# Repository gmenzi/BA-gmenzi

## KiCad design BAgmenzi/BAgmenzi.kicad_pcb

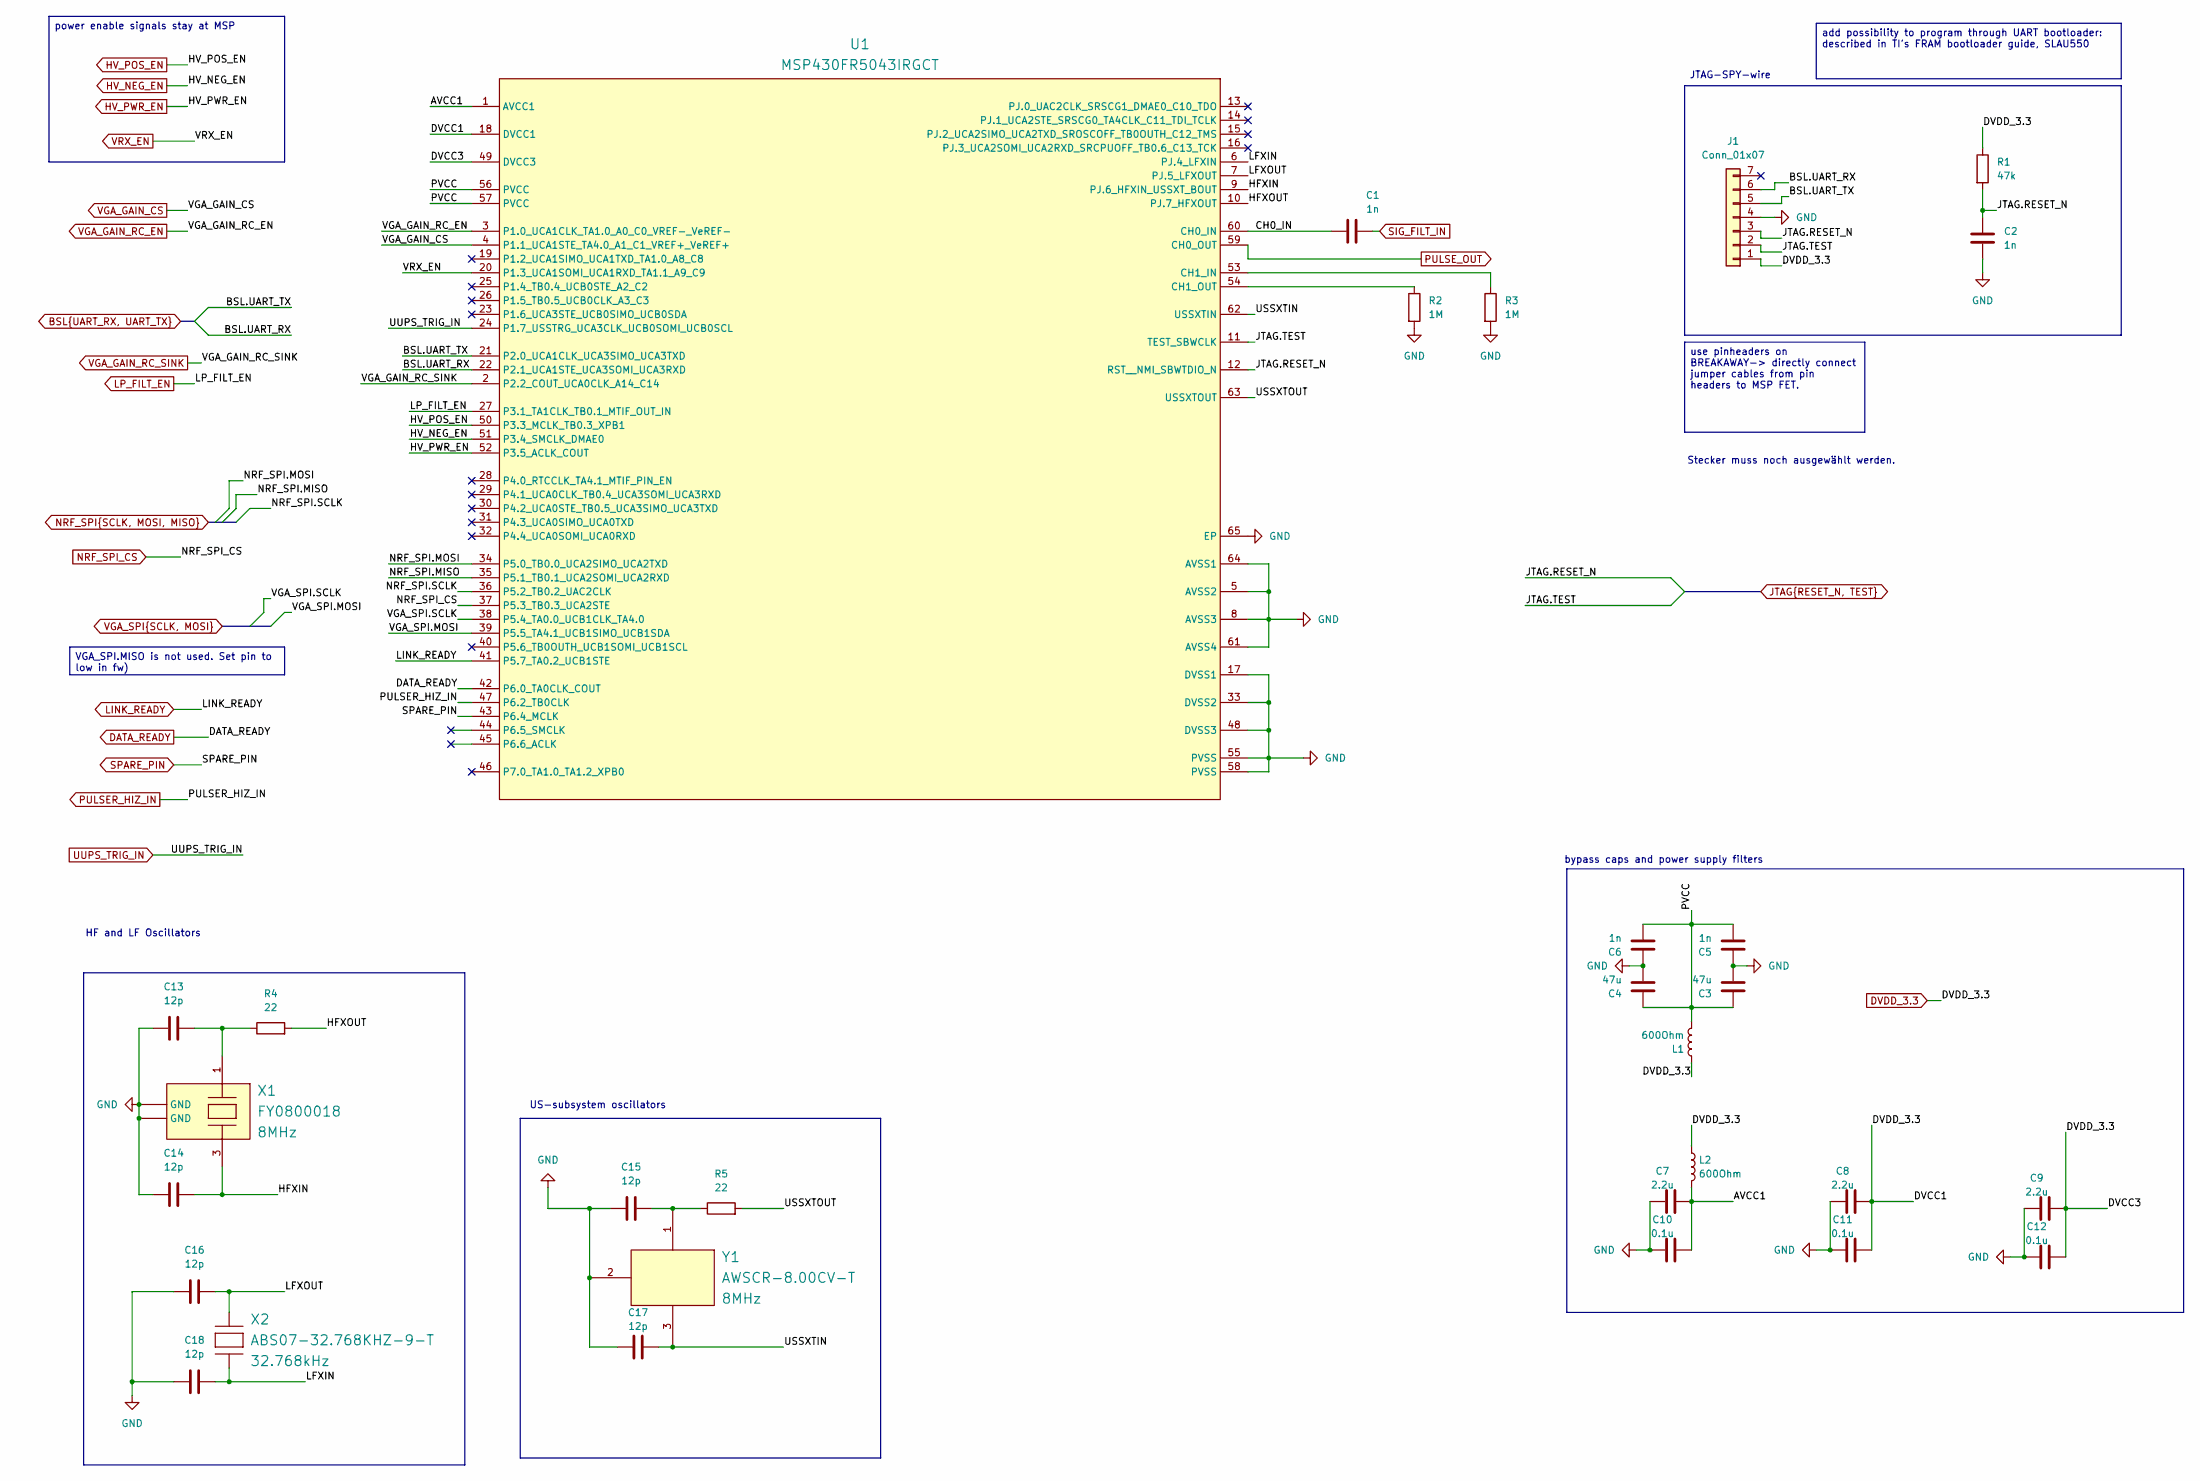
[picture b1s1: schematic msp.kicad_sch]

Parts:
C1, C2, C5, C6: 1n; C_0402_1005Metric; LCSC Part # C76947
C3, C4: 47u; C_0603_1608Metric; LCSC Part # C730416
C7, C8, C9: 2.2u; C_0402_1005Metric; LCSC Part # C77002
C10, C11, C12: 0.1u; C_0402_1005Metric; LCSC Part # C1525
C13, C14, C15, C16, C17, C18: 12p; C_0402_1005Metric; LCSC Part # C161305
J1: Conn_01x07; PinHeader_1x07_P2.54mm_Vertical_SMD_Pin1Right; LCSC Part # C2883764
L1, L2: 600Ohm; SMD-0805; LCSC Part # C41556732
R1: 47k; R_0402_1005Metric; LCSC Part # C482184
R2, R3: 1M; R_0402_1005Metric; LCSC Part # C413126
R4, R5: 22; R_0402_1005Metric; LCSC Part # C114765
U1: MSP430FR5043IRGCT; RGC0064G; Manufacturer_Part_Number MSP430FR5043IRGCT; LCSC Part # C5218420
X1: FY0800018; XTAL_ECS-80-18-30B-AGN-TR; Frequency Tolerance 30ppm; Manufacturer Part Number FY0800018; LCSC Part # C6951614
X2: ABS07-32.768KHZ-9-T; XTAL320X150X90; Frequency Tolerance 20ppm; Tolerance 20ppm; Manufacturer Part Number ABS07-32.768KHZ-9-T; LCSC Part # C179635
Y1: AWSCR-8.00CV-T; AWSCR-8.00CV-T_ABR; Manufacturer_Part_Number AWSCR-8.00CV-T; LCSC Part # C2650764

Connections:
/MSP/AVCC1: C7.2, C10.2, L2.2, U1.1 (AVCC1)
/MSP/CH0_IN: C1.1, U1.60 (CH0_IN)
/MSP/HFXIN: C14.2, U1.9 (PJ.6_HFXIN_USSXT_BOUT), X1.3 (OUT/IN)
/MSP/HFXOUT: R4.2, U1.10 (PJ.7_HFXOUT)
/MSP/LFXIN: C18.2, U1.6 (PJ.4_LFXIN), X2.1
/MSP/LFXOUT: C16.2, U1.7 (PJ.5_LFXOUT), X2.2
/MSP/PVCC: C3.1, C4.1, C5.2, C6.2, L1.2, U1.56 (PVCC), U1.57 (PVCC)
/MSP/USSXTIN: C17.2, U1.62 (USSXTIN), Y1.3
/MSP/USSXTOUT: R5.2, U1.63 (USSXTOUT)
BSL.UART_RX: J1.6, U1.22 (P2.1_UCA1STE_UCA3SOMI_UCA3RXD); also elsewhere on the board
BSL.UART_TX: J1.5, U1.21 (P2.0_UCA1CLK_UCA3SIMO_UCA3TXD); also elsewhere on the board
DATA_READY: U1.42 (P6.0_TA0CLK_COUT); also elsewhere on the board
DVDD_3.3: C8.2, C9.2, C11.2, C12.2, J1.1, L1.1, L2.1, R1.1, U1.18 (DVCC1), U1.49 (DVCC3); also elsewhere on the board
GND: C2.2, C3.2, C4.2, C5.1, C6.1, C7.1, C8.1, C9.1, C10.1, C11.1, C12.1, C13.1, C14.1, C15.1, C16.1, C17.1, C18.1, J1.4, R2.2, R3.2, U1.5 (AVSS2), U1.8 (AVSS3), U1.17 (DVSS1), U1.33 (DVSS2), U1.48 (DVSS3), U1.55 (PVSS), U1.58 (PVSS), U1.61 (AVSS4), U1.64 (AVSS1), U1.65 (EP), X1.2 (GND), X1.4 (GND), Y1.2; also elsewhere on the board
HV_NEG_EN: U1.51 (P3.4_SMCLK_DMAE0); also elsewhere on the board
HV_POS_EN: U1.50 (P3.3_MCLK_TB0.3_XPB1); also elsewhere on the board
HV_PWR_EN: U1.52 (P3.5_ACLK_COUT); also elsewhere on the board
JTAG.RESET_N: C2.1, J1.3, R1.2, U1.12 (RST__NMI_SBWTDIO_N); also elsewhere on the board
JTAG.TEST: J1.2, U1.11 (TEST_SBWCLK); also elsewhere on the board
LINK_READY: U1.41 (P5.7_TA0.2_UCB1STE); also elsewhere on the board
LP_FILT_EN: U1.27 (P3.1_TA1CLK_TB0.1_MTIF_OUT_IN); also elsewhere on the board
NRF_SPI.MISO: U1.35 (P5.1_TB0.1_UCA2SOMI_UCA2RXD); also elsewhere on the board
NRF_SPI.MOSI: U1.34 (P5.0_TB0.0_UCA2SIMO_UCA2TXD); also elsewhere on the board
NRF_SPI.SCLK: U1.36 (P5.2_TB0.2_UAC2CLK); also elsewhere on the board
NRF_SPI_CS: U1.37 (P5.3_TB0.3_UCA2STE); also elsewhere on the board
unnamed: C15.2, R5.1, Y1.1
unnamed: R3.1, U1.53 (CH1_IN)
unnamed: R2.1, U1.54 (CH1_OUT)
unnamed: C13.2, R4.1, X1.1 (IN/OUT)
PULSER_HIZ_IN: U1.47 (P6.2_TB0CLK); also elsewhere on the board
PULSE_OUT: U1.59 (CH0_OUT); also elsewhere on the board
SIG_FILT_IN: C1.2; also elsewhere on the board
SPARE_PIN: U1.43 (P6.4_MCLK); also elsewhere on the board
UUPS_TRIG_IN: U1.24 (P1.7_USSTRG_UCA3CLK_UCB0SOMI_UCB0SCL); also elsewhere on the board
VGA_GAIN_CS: U1.4 (P1.1_UCA1STE_TA4.0_A1_C1_VREF+_VeREF+); also elsewhere on the board
VGA_GAIN_RC_EN: U1.3 (P1.0_UCA1CLK_TA1.0_A0_C0_VREF-_VeREF-); also elsewhere on the board
VGA_GAIN_RC_SINK: U1.2 (P2.2_COUT_UCA0CLK_A14_C14); also elsewhere on the board
VGA_SPI.MOSI: U1.39 (P5.5_TA4.1_UCB1SIMO_UCB1SDA); also elsewhere on the board
VGA_SPI.SCLK: U1.38 (P5.4_TA0.0_UCB1CLK_TA4.0); also elsewhere on the board
VRX_EN: U1.20 (P1.3_UCA1SOMI_UCA1RXD_TA1.1_A9_C9); also elsewhere on the board

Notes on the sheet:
bypass caps and power supply filters
US-subsystem oscillators
JTAG-SPY-wire
Stecker muss noch ausgewählt werden.
HF and LF Oscillators
use pinheaders on BREAKAWAY-> directly connect jumper cables from pin headers to MSP FET.
VGA_SPI.MISO is not used. Set pin to low in fw)
add possibility to program through UART bootloader: described in TI's FRAM bootloader guide, SLAU550
power enable signals stay at MSP

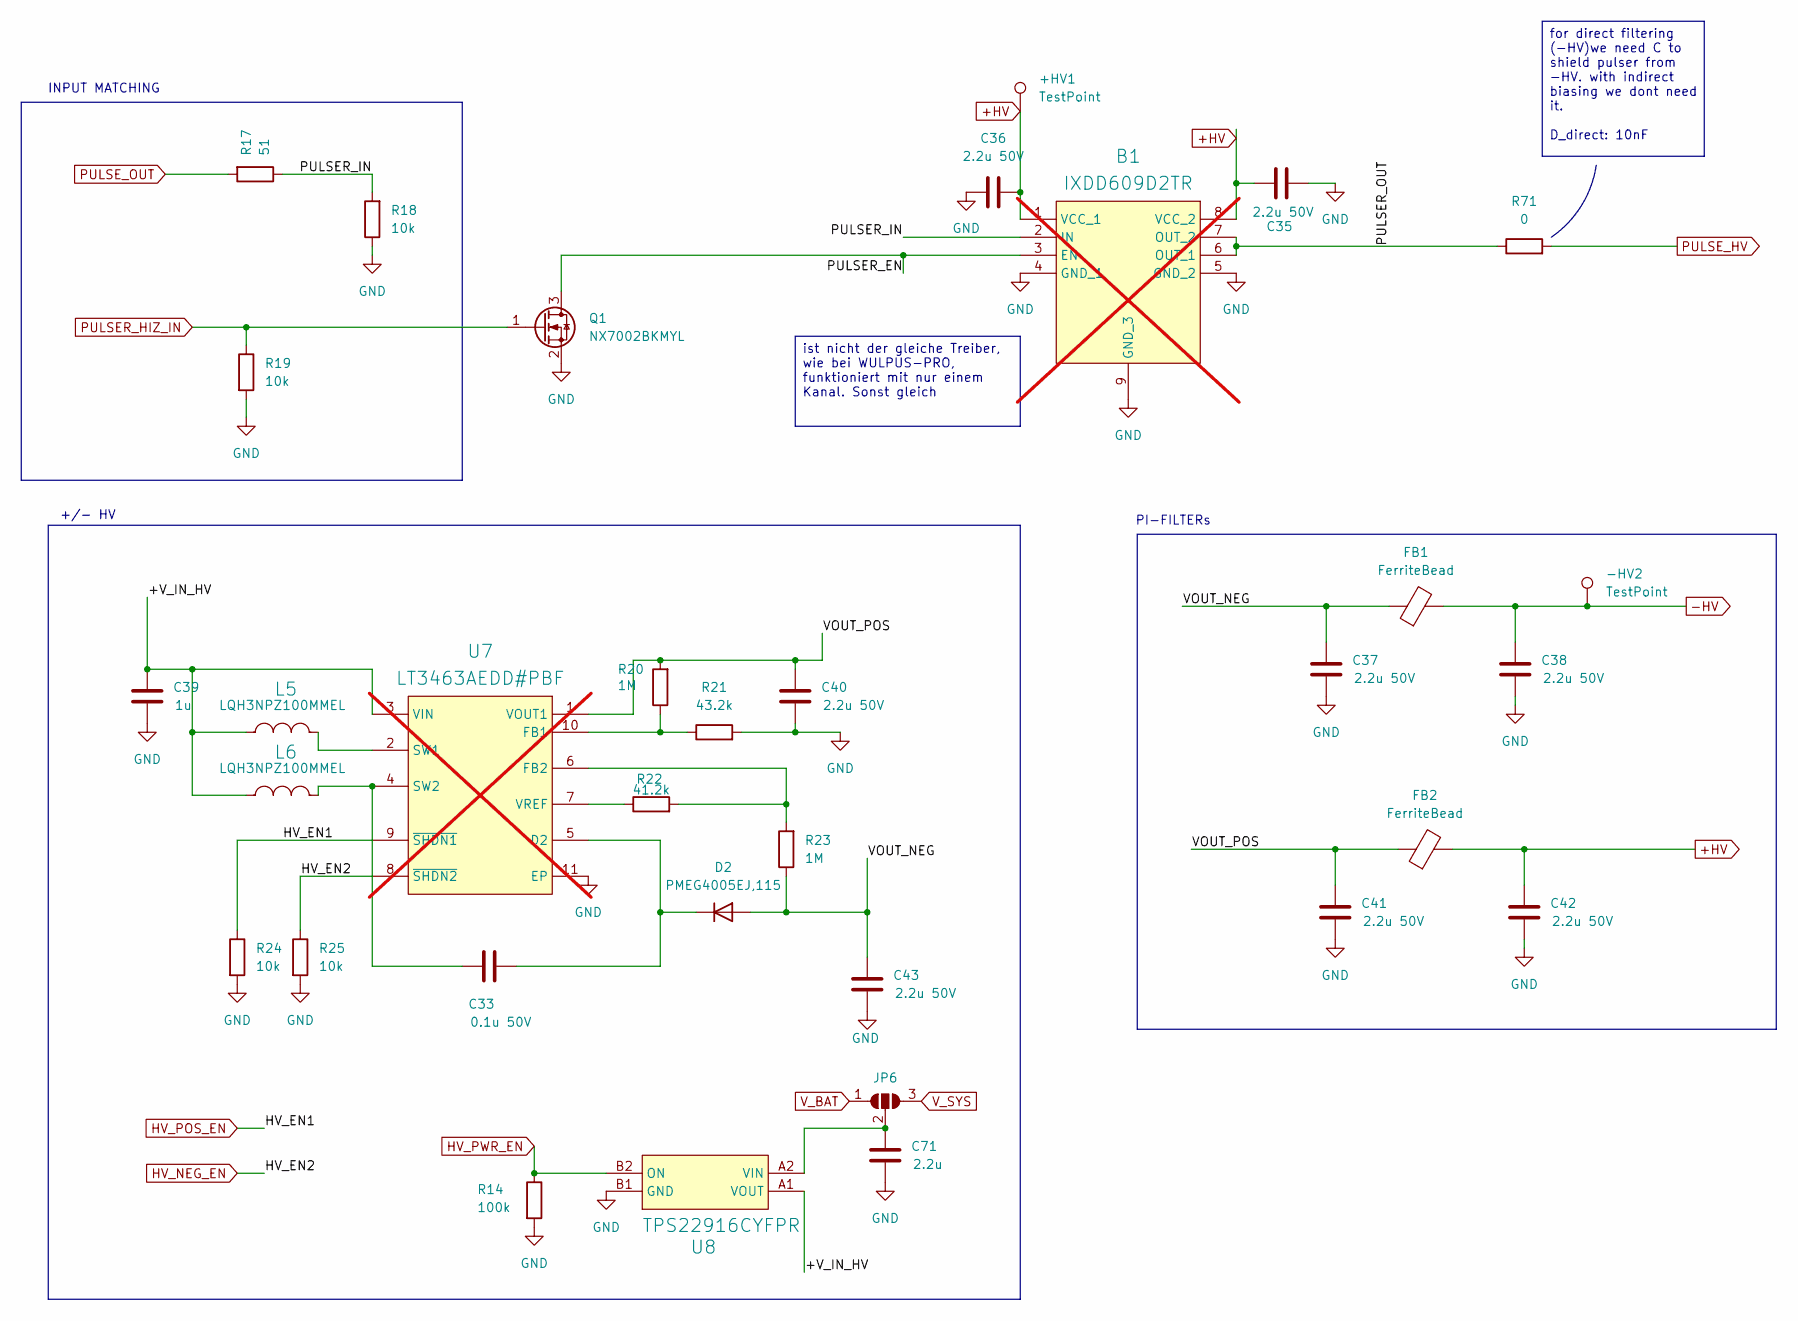
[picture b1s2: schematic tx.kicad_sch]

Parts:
+HV1: TestPoint; TestPoint_Pad_D1.0mm
-HV2: TestPoint; TestPoint_Pad_D1.0mm
B1: IXDD609D2TR; SON95P500X400X100-9N; Manufacturer_Part_Number IXDD609D2TR; LCSC Part # C2653792; not fitted
C33: 0.1u 50V; C_0402_1005Metric; LCSC Part # C913614
C35, C36, C37, C38, C40, C41, C42, C43: 2.2u 50V; C_0603_1608Metric; LCSC Part # C668357
C39: 1u; C_0402_1005Metric; LCSC Part # C14445
C71: 2.2u; C_0402_1005Metric; LCSC Part # C77002
D2: PMEG4005EJ,115; D_SOD-323_HandSoldering; LCSC Part # C426868
FB1, FB2: FerriteBead; L_0603_1608Metric; LCSC Part # C3717002
JP6: SolderJumper_3_Open; SolderJumper-3_P1.3mm_Open_Pad1.0x1.5mm
L5, L6: LQH3NPZ100MMEL; FP-LQH3NPH_ME-MFG; Current Rating 170mA; Manufacturer Part Number LQP15MN3N9B02D; LCSC Part # C701168
Q1: NX7002BKMYL; NX7002BKMBYL; LCSC Part # C551611
R14: 100k; R_0402_1005Metric; LCSC Part # C192169
R17: 51; R_0402_1005Metric; LCSC Part # C482204
R18, R19, R24, R25: 10k; R_0402_1005Metric; LCSC Part # C191984
R20, R23: 1M; R_0402_1005Metric; LCSC Part # C413126
R21: 43.2k; R_0402_1005Metric; LCSC Part # C278596
R22: 41.2k; R_0402_1005Metric; LCSC Part # C416536
R71: 0; R_0402_1005Metric; LCSC Part # C190119
U7: LT3463AEDD#PBF; LT-DD-10_V; PartNumber LT3463AEDD#PBF; LCSC Part # C580060; not fitted
U8: TPS22916CYFPR; BGA4C40P2X2_78X78X50; Manufacturer_Part_Number TPS22916CYFPR; LCSC Part # C2680319

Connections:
+HV: +HV1.1, B1.1 (VCC_1), B1.8 (VCC_2), C35.2, C36.2, C42.1, FB2.2; also elsewhere on the board
-HV: -HV2.1, C38.1, FB1.2; also elsewhere on the board
/TX/+V_IN_HV: C39.1, L5.1, L6.1, U7.3 (VIN), U8.A1 (VOUT)
/TX/PULSER_EN: B1.3 (EN), Q1.3 (D)
/TX/PULSER_IN: B1.2 (IN), R17.1, R18.2
/TX/PULSER_OUT: B1.6 (OUT_1), B1.7 (OUT_2), R71.1
/TX/VOUT_NEG: C37.1, C43.1, D2.2 (A), FB1.1, R23.1
/TX/VOUT_POS: C40.1, C41.1, FB2.1, R20.2, U7.1 (VOUT1)
GND: B1.4 (GND_1), B1.5 (GND_2), B1.9 (GND_3), C35.1, C36.1, C37.2, C38.2, C39.2, C40.2, C41.2, C42.2, C43.2, C71.2, Q1.2 (S), R14.2, R18.1, R19.2, R21.2, R24.2, R25.2, U7.11 (EP), U8.B1 (GND); also elsewhere on the board
HV_NEG_EN: R25.1, U7.8 (~SHDN2); also elsewhere on the board
HV_POS_EN: R24.1, U7.9 (~SHDN1); also elsewhere on the board
HV_PWR_EN: R14.1, U8.B2 (ON); also elsewhere on the board
unnamed: C33.1, D2.1 (K), U7.5 (D2)
unnamed: C71.1, JP6.2 (C), U8.A2 (VIN)
unnamed: R20.1, R21.1, U7.10 (FB1)
unnamed: R22.2, R23.2, U7.6 (FB2)
unnamed: L5.2, U7.2 (SW1)
unnamed: C33.2, L6.2, U7.4 (SW2)
unnamed: R22.1, U7.7 (VREF)
PULSER_HIZ_IN: Q1.1 (G), R19.1; also elsewhere on the board
PULSE_HV: R71.2; also elsewhere on the board
PULSE_OUT: R17.2; also elsewhere on the board
V_BAT: JP6.1 (A); also elsewhere on the board
V_SYS: JP6.3 (B); also elsewhere on the board

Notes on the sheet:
INPUT MATCHING
+/- HV
PI-FILTERs
ist nicht der gleiche Treiber, wie bei WULPUS-PRO, funktioniert mit nur einem Kanal. Sonst gleich
for direct filtering (-HV)we need C to shield pulser from -HV. with indirect biasing we dont need it. D_direct: 10nF

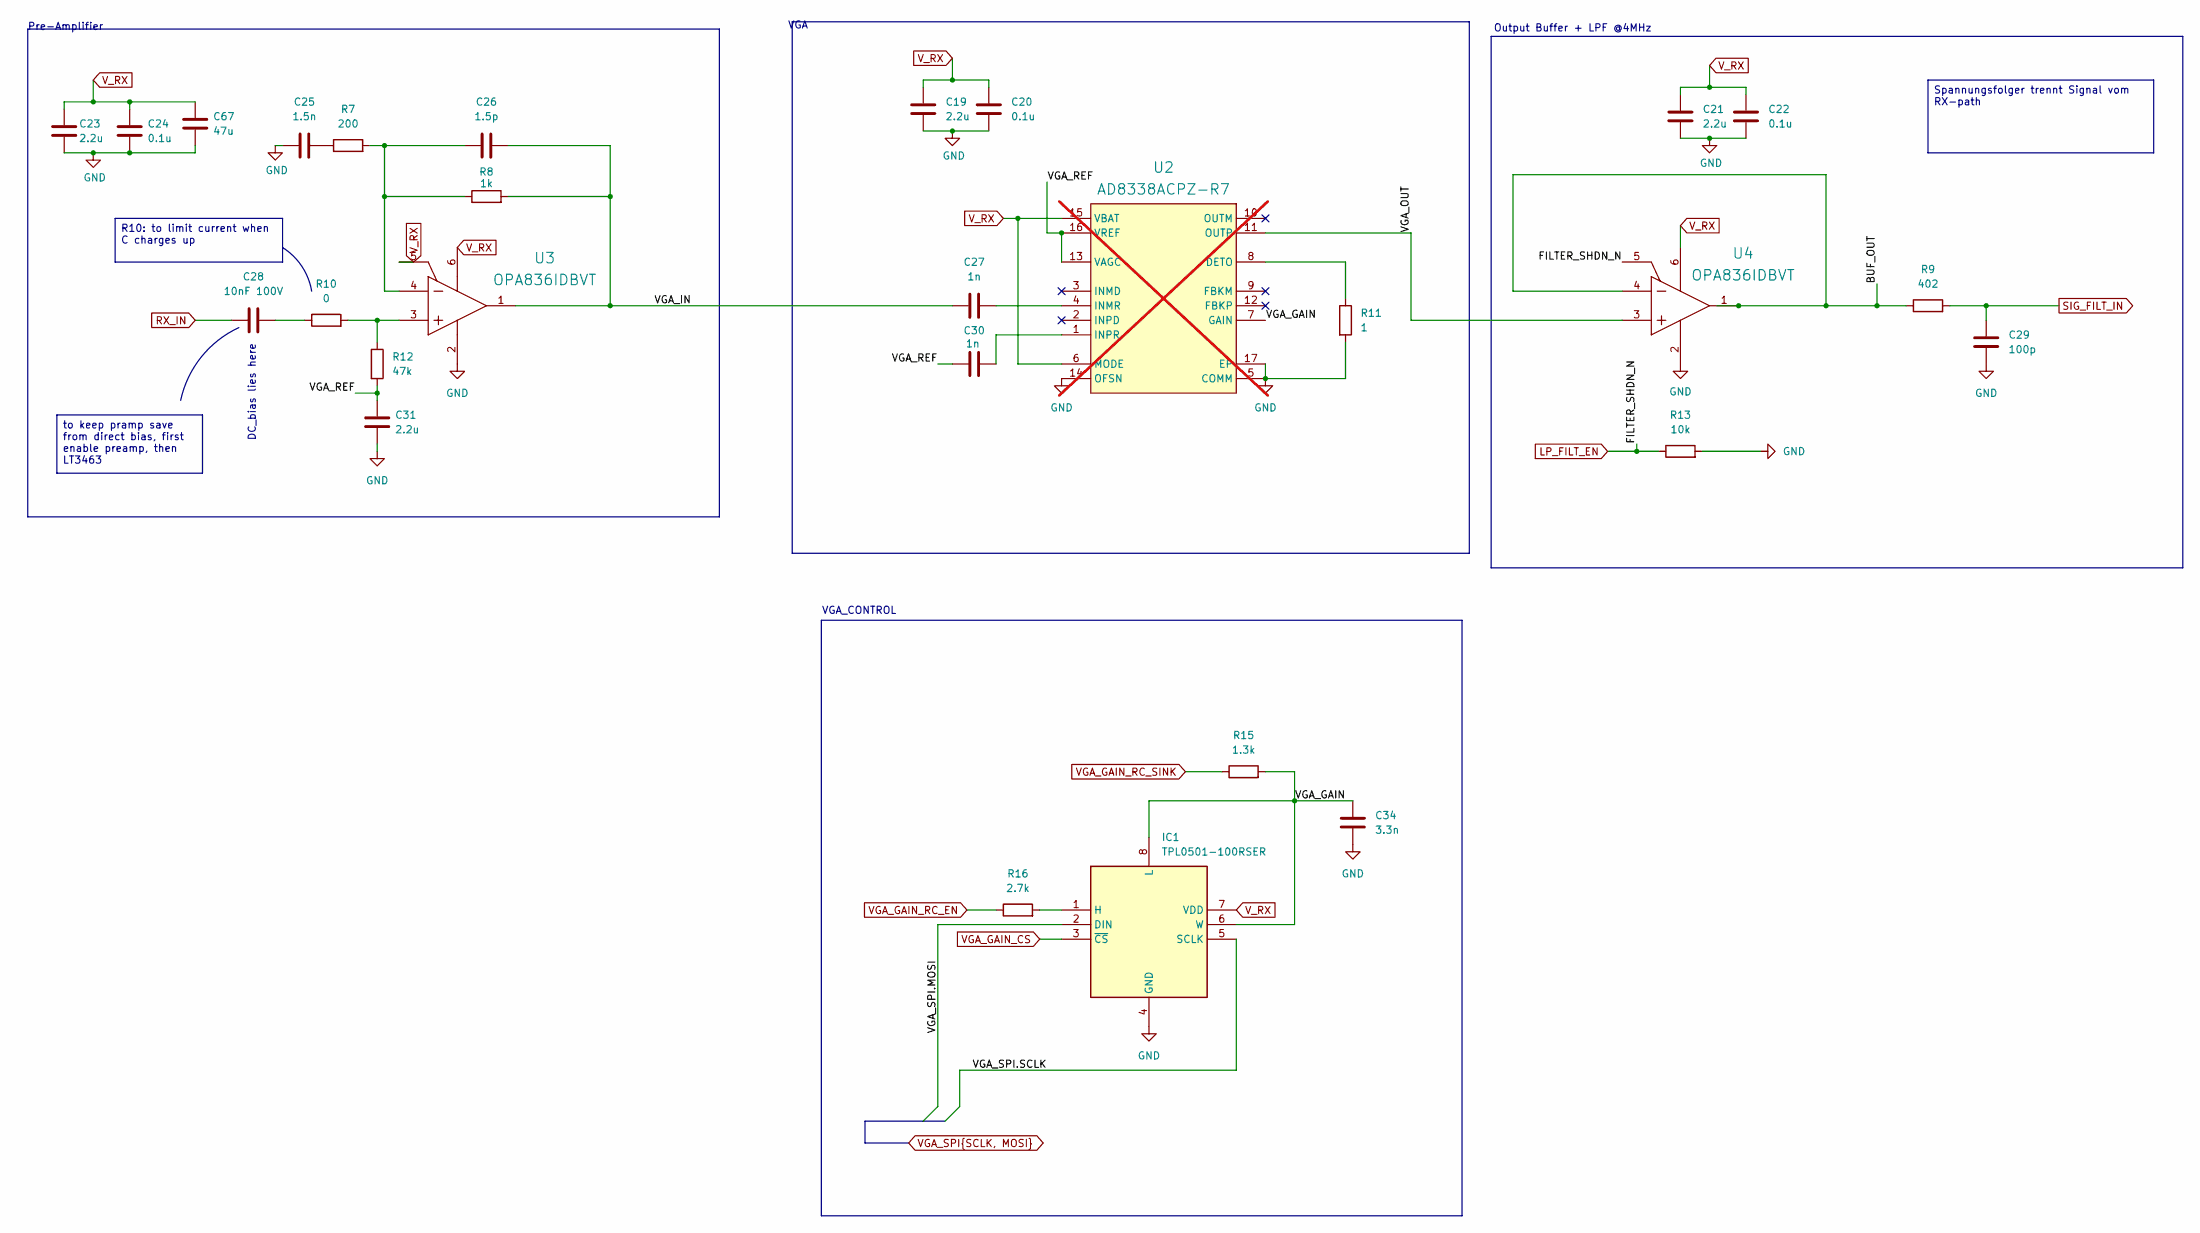
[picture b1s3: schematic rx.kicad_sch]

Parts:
C19, C21, C23, C31: 2.2u; C_0402_1005Metric; LCSC Part # C77002
C20, C22, C24: 0.1u; C_0402_1005Metric; LCSC Part # C1525
C25: 1.5n; C_0402_1005Metric; LCSC Part # C23967
C26: 1.5p; C_0402_1005Metric; LCSC Part # C76900
C27, C30: 1n; C_0402_1005Metric; LCSC Part # C76947
C28: 10nF 100V; C_0402_1005Metric; LCSC Part # C2167243
C29: 100p; C_0402_1005Metric; LCSC Part # C1546
C34: 3.3n; C_0402_1005Metric; LCSC Part # C26404
C67: 47u; C_0603_1608Metric; LCSC Part # C730416
IC1: TPL0501-100RSER; RSE0008A; Manufacturer_Part_Number TPL0501-100RSER; Mouser Part Number 595-TPL0501-100RSER
R7: 200; R_0402_1005Metric; LCSC Part # C25087
R8: 1k; R_0402_1005Metric; LCSC Part # C11702
R9: 402; R_0402_1005Metric; LCSC Part # C41042
R10: 0; R_0402_1005Metric; LCSC Part # C190119
R11: 1; R_0402_1005Metric; LCSC Part # C2077765
R12: 47k; R_0402_1005Metric; LCSC Part # C482184
R13: 10k; R_0402_1005Metric; LCSC Part # C191984
R15: 1.3k; R_0402_1005Metric; LCSC Part # C25866
R16: 2.7k; R_0402_1005Metric; LCSC Part # C2074348
U2: AD8338ACPZ-R7; FP-CP-16-22-IPC_C; Voltage Gain 80dB; Manufacturer Part Number AD8338ACPZ-R7; Mouser Description Special Purpose Amplifiers Ultra Low Pw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; not fitted
U3, U4: OPA836IDBVT; DBV0006A_L; PartNumber OPA836IDBVT; LCSC Part # C2057515

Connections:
/RX/BUF_OUT: R9.1, U4.1 (VOUT), U4.4 (VIN-)
/RX/VGA_GAIN: C34.2, IC1.6 (W), IC1.8 (L), R15.2, U2.7 (GAIN)
/RX/VGA_IN: C26.2, C27.1, R8.2, U3.1 (VOUT)
/RX/VGA_OUT: U2.11 (OUTP), U4.3 (VIN+)
/RX/VGA_REF: C30.1, C31.2, R12.2, U2.13 (VAGC), U2.16 (VREF)
GND: C19.1, C20.1, C21.1, C22.1, C23.1, C24.1, C25.1, C29.1, C31.1, C34.1, C67.1, IC1.4 (GND), R11.2, R13.2, U2.5 (COMM), U2.14 (OFSN), U2.17 (EP), U3.2 (VS-), U4.2 (VS-); also elsewhere on the board
LP_FILT_EN: R13.1, U4.5 (~PD); also elsewhere on the board
unnamed: C25.2, R7.1
unnamed: C28.2, R10.1
unnamed: IC1.1 (H), R16.2
unnamed: R11.1, U2.8 (DETO)
unnamed: C27.2, U2.4 (INMR)
unnamed: C30.2, U2.1 (INPR)
unnamed: R10.2, R12.1, U3.3 (VIN+)
unnamed: C26.1, R7.2, R8.1, U3.4 (VIN-)
RX_IN: C28.1; also elsewhere on the board
SIG_FILT_IN: C29.2, R9.2; also elsewhere on the board
VGA_GAIN_CS: IC1.3 (~CS); also elsewhere on the board
VGA_GAIN_RC_EN: R16.1; also elsewhere on the board
VGA_GAIN_RC_SINK: R15.1; also elsewhere on the board
VGA_SPI.MOSI: IC1.2 (DIN); also elsewhere on the board
VGA_SPI.SCLK: IC1.5 (SCLK); also elsewhere on the board
V_RX: C19.2, C20.2, C21.2, C22.2, C23.2, C24.2, C67.2, IC1.7 (VDD), U2.6 (MODE), U2.15 (VBAT), U3.5 (~PD), U3.6 (VS+), U4.6 (VS+); also elsewhere on the board

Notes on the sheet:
Output Buffer + LPF @4MHz
VGA
VGA_CONTROL
Pre-Amplifier
DC_bias lies here
R10: to limit current when C charges up
Spannungsfolger trennt Signal vom RX-path
to keep pramp save from direct bias, first enable preamp, then LT3463

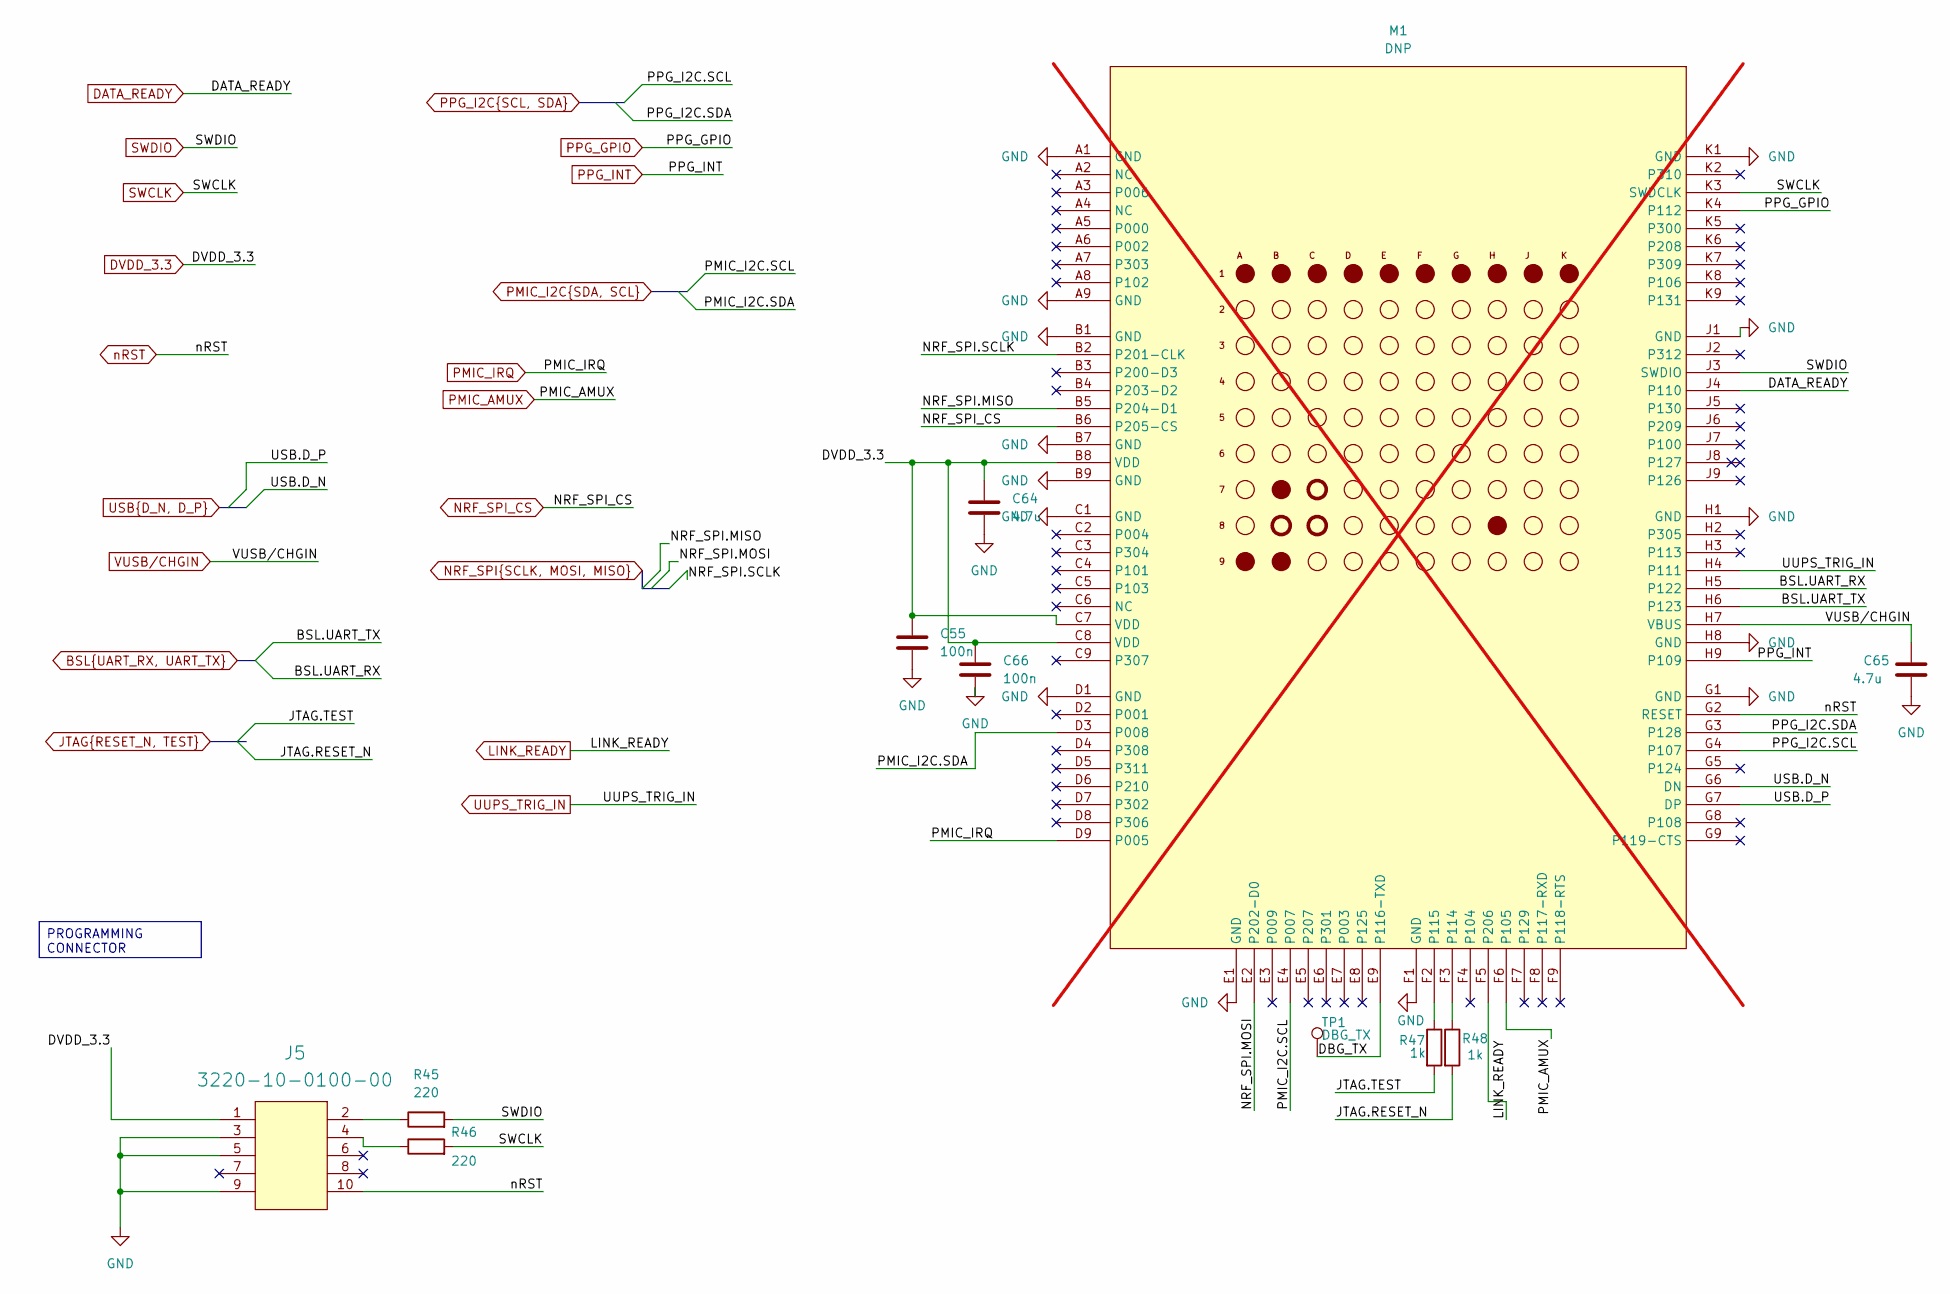
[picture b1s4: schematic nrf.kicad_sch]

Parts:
C55, C66: 100n; C_0402_1005Metric; LCSC Part # C1525
C64, C65: 4.7u; C_0402_1005Metric; LCSC Part # C23733
J5: 3220-10-0100-00; PinHeader_2x05_P1.27mm_Vertical_SMD; Manufacturer_Part_Number 3220-10-0100-00; LCSC Part # C5382952
M1: DNP; BM20-C; not fitted
R45, R46: 220; 0402; LCSC Part # C25091
R47, R48: 1k; R_0402_1005Metric; LCSC Part # C11702
TP1: DBG_TX; TestPoint_Pad_D1.0mm

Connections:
/NRF/DBG_TX: M1.E9 (P116-TXD), TP1.1
BSL.UART_RX: M1.H5 (P122); also elsewhere on the board
BSL.UART_TX: M1.H6 (P123); also elsewhere on the board
DATA_READY: M1.J4 (P110); also elsewhere on the board
DVDD_3.3: C55.1, C64.1, C66.1, J5.1, M1.B8 (VDD), M1.C7 (VDD), M1.C8 (VDD); also elsewhere on the board
GND: C55.2, C64.2, C65.2, C66.2, J5.3, J5.5, J5.9, M1.A1 (GND), M1.A9 (GND), M1.B1 (GND), M1.B7 (GND), M1.B9 (GND), M1.C1 (GND), M1.D1 (GND), M1.E1 (GND), M1.F1 (GND), M1.G1 (GND), M1.H1 (GND), M1.H8 (GND), M1.J1 (GND), M1.K1 (GND); also elsewhere on the board
JTAG.RESET_N: R48.2; also elsewhere on the board
JTAG.TEST: R47.2; also elsewhere on the board
LINK_READY: M1.F5 (P206); also elsewhere on the board
NRF_SPI.MISO: M1.B5 (P204-D1); also elsewhere on the board
NRF_SPI.MOSI: M1.E2 (P202-D0); also elsewhere on the board
NRF_SPI.SCLK: M1.B2 (P201-CLK); also elsewhere on the board
NRF_SPI_CS: M1.B6 (P205-CS); also elsewhere on the board
unnamed: J5.2, R45.1
unnamed: J5.4, R46.1
unnamed: M1.F3 (P114), R48.1
unnamed: M1.F2 (P115), R47.1
PMIC_AMUX: M1.F6 (P105); also elsewhere on the board
PMIC_I2C.SCL: M1.E4 (P007); also elsewhere on the board
PMIC_I2C.SDA: M1.D3 (P008); also elsewhere on the board
PMIC_IRQ: M1.D9 (P005); also elsewhere on the board
PPG_GPIO: M1.K4 (P112); also elsewhere on the board
PPG_I2C.SCL: M1.G4 (P107); also elsewhere on the board
PPG_I2C.SDA: M1.G3 (P128); also elsewhere on the board
PPG_INT: M1.H9 (P109); also elsewhere on the board
SWCLK: M1.K3 (SWDCLK), R46.2
SWDIO: M1.J3 (SWDIO), R45.2
USB.D_N: M1.G6 (DN); also elsewhere on the board
USB.D_P: M1.G7 (DP); also elsewhere on the board
UUPS_TRIG_IN: M1.H4 (P111); also elsewhere on the board
VUSB/CHGIN: C65.1, M1.H7 (VBUS); also elsewhere on the board
nRST: J5.10, M1.G2 (RESET); also elsewhere on the board

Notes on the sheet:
PROGRAMMING CONNECTOR

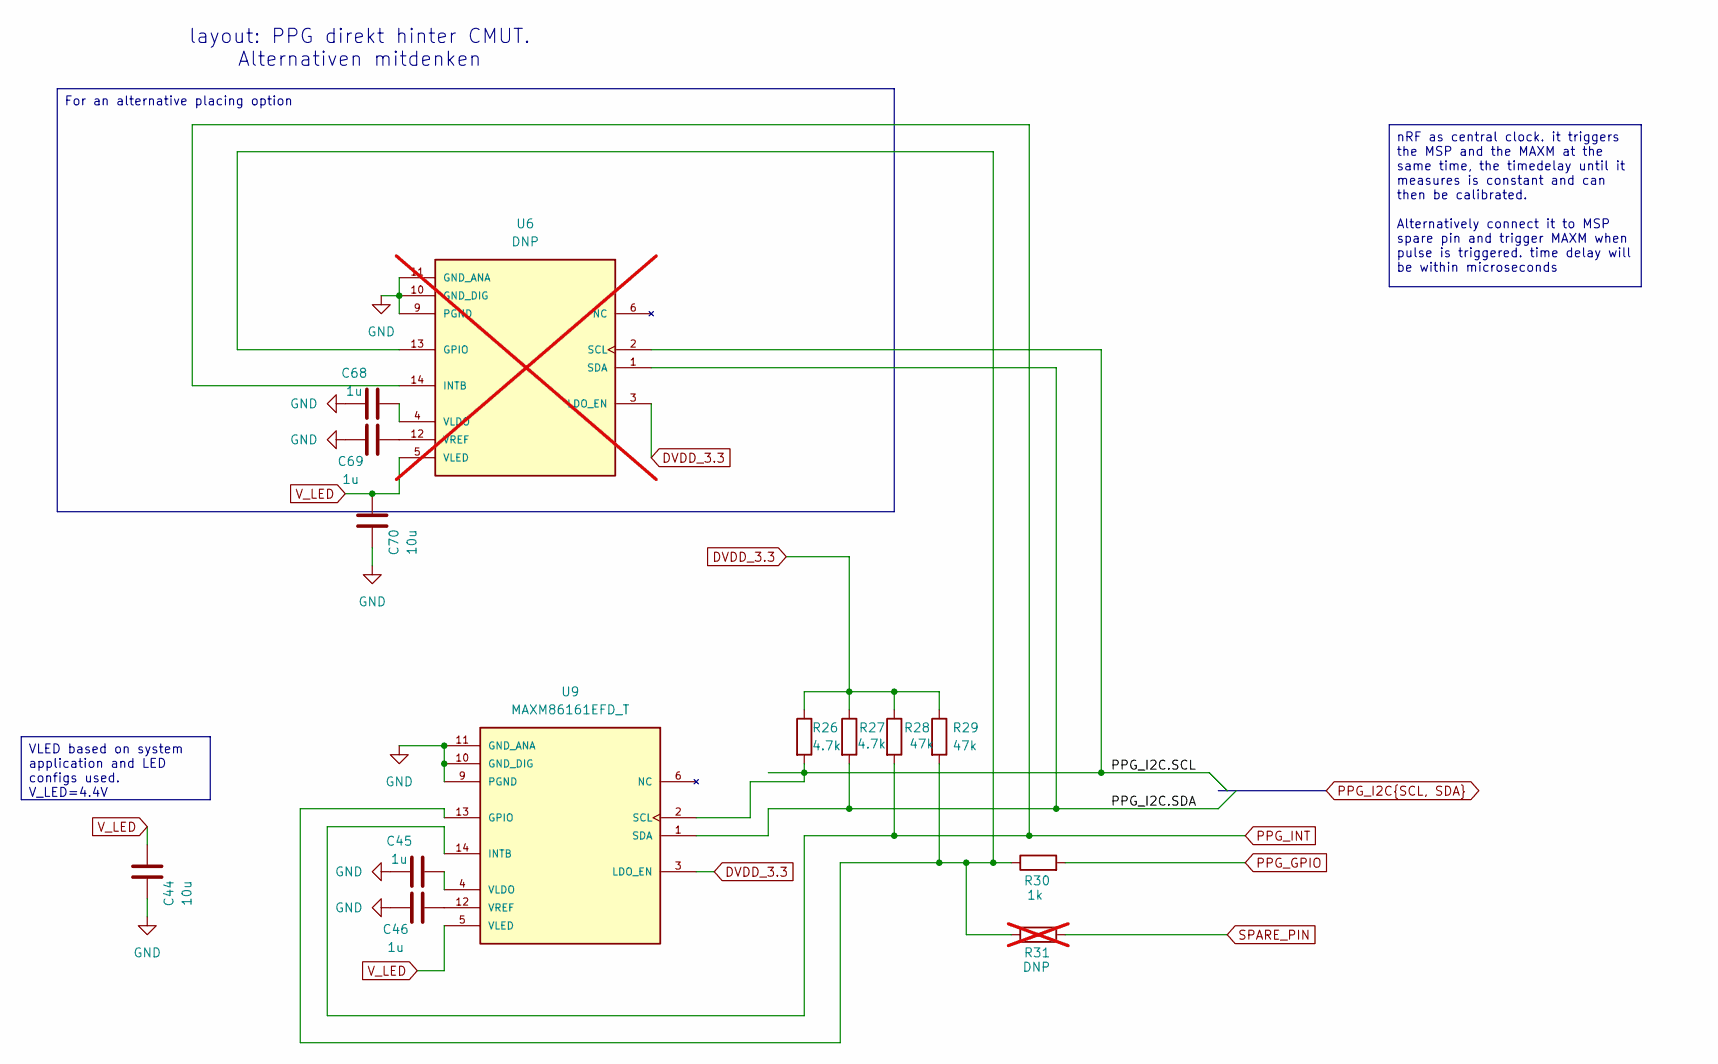
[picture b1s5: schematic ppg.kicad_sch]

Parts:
C44, C70: 10u; C_0402_1005Metric; LCSC Part # C15525
C45, C46, C68, C69: 1u; C_0402_1005Metric; LCSC Part # C14445
R26, R27: 4.7k; R_0402_1005Metric; LCSC Part # C25900
R28, R29: 47k; R_0402_1005Metric; LCSC Part # C482184
R30: 1k; R_0402_1005Metric; LCSC Part # C11702
R31: DNP; R_0402_1005Metric; not fitted
U6: DNP; PSON60P430X290X150-14N; PARTREV 1; not fitted
U9: MAXM86161EFD_T; PSON60P430X290X150-14N; PARTREV 1; LCSC Part # C3178309

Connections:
DVDD_3.3: R26.1, R27.1, R28.1, R29.1, U6.3 (LDO_EN), U9.3 (LDO_EN); also elsewhere on the board
GND: C44.1, C45.1, C46.1, C68.1, C69.1, C70.1, U6.9 (PGND), U6.10 (GND_DIG), U6.11 (GND_ANA), U9.9 (PGND), U9.10 (GND_DIG), U9.11 (GND_ANA); also elsewhere on the board
unnamed: R29.2, R30.1, R31.1, U6.13 (GPIO), U9.13 (GPIO)
unnamed: C68.2, U6.4 (VLDO)
unnamed: C69.2, U6.12 (VREF)
unnamed: C45.2, U9.4 (VLDO)
unnamed: C46.2, U9.12 (VREF)
PPG_GPIO: R30.2; also elsewhere on the board
PPG_I2C.SCL: R26.2, U6.2 (SCL), U9.2 (SCL); also elsewhere on the board
PPG_I2C.SDA: R27.2, U6.1 (SDA), U9.1 (SDA); also elsewhere on the board
PPG_INT: R28.2, U6.14 (INTB), U9.14 (INTB); also elsewhere on the board
SPARE_PIN: R31.2; also elsewhere on the board
V_LED: C44.2, C70.2, U6.5 (VLED), U9.5 (VLED); also elsewhere on the board

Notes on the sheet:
layout: PPG direkt hinter CMUT. Alternativen mitdenken
For an alternative placing option
VLED based on system application and LED configs used. V_LED=4.4V
nRF as central clock. it triggers the MSP and the MAXM at the same time, the timedelay until it measures is constant and can then be calibrated. Alternatively connect it to MSP spare pin and trigger MAXM when pulse is triggered. time delay will be within microseconds

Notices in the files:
parts and their libraries:
Copyright: Copyright (C) 2021 Ultra Librarian. All rights reserved.
Copyright: Copyright (C) 2023 Ultra Librarian. All rights reserved.
